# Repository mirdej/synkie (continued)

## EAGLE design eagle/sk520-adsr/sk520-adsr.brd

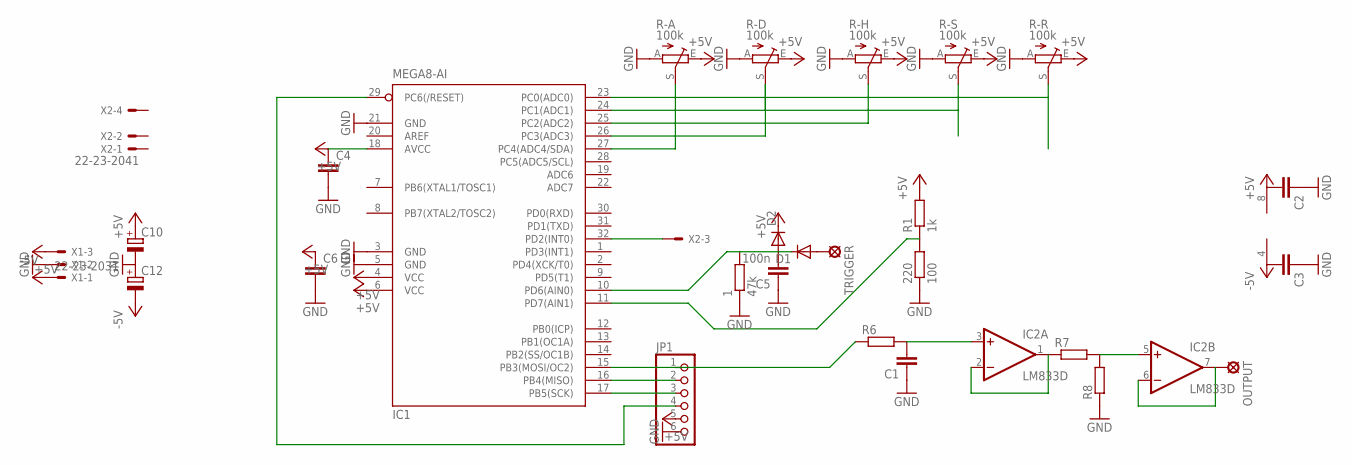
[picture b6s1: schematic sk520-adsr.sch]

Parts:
1: 47k; R1206
220: 100; R1206
C1, C2, C3, C4, C6: C-EUC1206; C1206
C5: 100n; C1206
C10, C12: CPOL-EUCT6032; CT6032
D1, D2: DIODE-MINIMELF; MINIMELF
IC1: MEGA8-AI; TQFP32-08
IC2: LM833D; SO08
JP1: PINHD-1X6; 1X06
OUTPUT: LSP11
R1: 1k; R1206
R6, R7, R8: R-EU_R1206; R1206
R-A: 100k; CIP20C-6MM
R-D: 100k; CIP20C-6MM
R-H: 100k; CIP20C-6MM
R-R: 100k; CIP20C-6MM
R-S: 100k; CIP20C-6MM
TRIGGER: LSP11
X1: 22-23-2031
X2: 22-23-2041

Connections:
+5V: C2.2, C4.1, C6.1, C10.+, D2.C, IC1.4 (VCC), IC1.6 (VCC), IC1.18 (AVCC), IC2.8 (V+), JP1.5, R1.2, R-A.E, R-D.E, R-H.E, R-R.E, R-S.E, X1.3
-5V: C3.2, C12.-, IC2.4 (V-), X1.1
GND: 1.1, 220.1, C1.1, C2.1, C3.1, C4.2, C5.1, C6.2, C10.-, C12.+, IC1.3 (GND), IC1.5 (GND), IC1.21 (GND), JP1.6, R8.1, R-A.A, R-D.A, R-H.A, R-R.A, R-S.A, X1.2
unnamed: IC1.15 (PB3(MOSI/OC2)), JP1.1, R6.1
unnamed: D1.A, TRIGGER.MP
unnamed: IC1.16 (PB4(MISO)), JP1.2
unnamed: IC1.17 (PB5(SCK)), JP1.3
unnamed: IC1.29 (PC6(/RESET)), JP1.4
unnamed: IC1.27 (PC4(ADC4/SDA)), R-A.S
unnamed: IC1.26 (PC3(ADC3)), R-D.S
unnamed: IC1.25 (PC2(ADC2)), R-H.S
unnamed: IC1.24 (PC1(ADC1)), R-S.S
unnamed: IC1.23 (PC0(ADC0)), R-R.S
unnamed: 1.2, C5.2, D1.C, D2.A, IC1.10 (PD6(AIN0))
unnamed: C1.2, IC2.3 (+IN), R6.2
unnamed: IC2.1 (OUT), IC2.2 (-IN), R7.1
unnamed: IC2.5 (+IN), R7.2, R8.2
unnamed: IC2.6 (-IN), IC2.7 (OUT), OUTPUT.MP
unnamed: 220.2, IC1.11 (PD7(AIN1)), R1.1
TRIGGER: IC1.32 (PD2(INT0)), X2.3

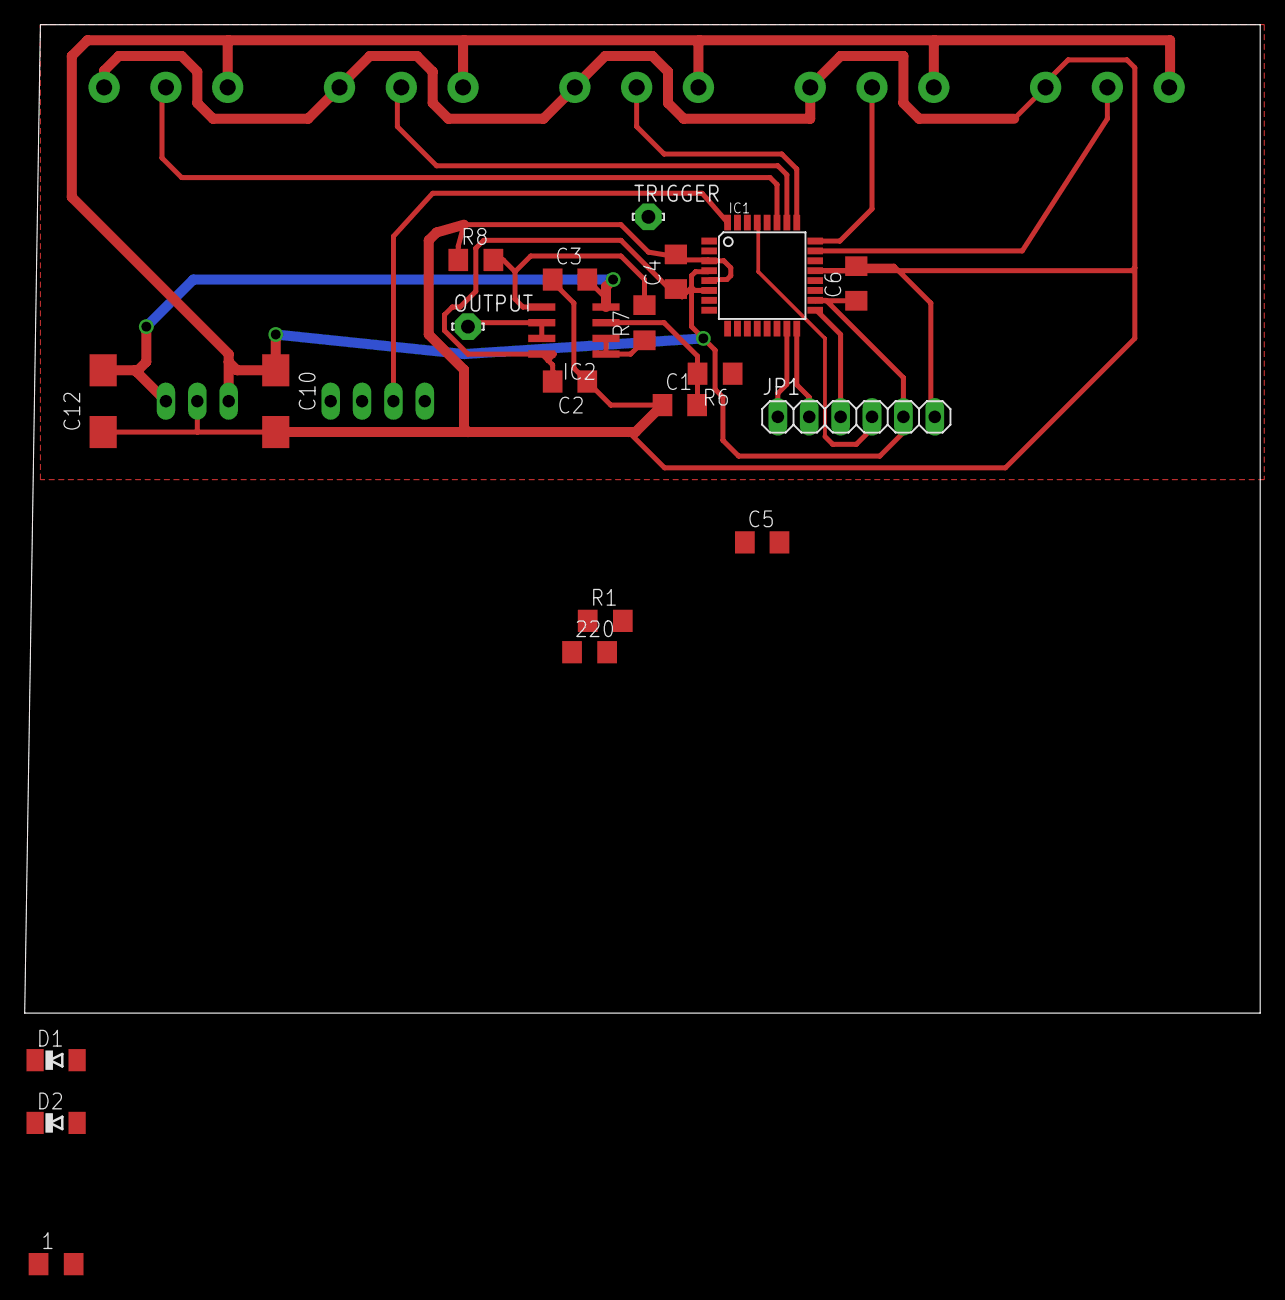
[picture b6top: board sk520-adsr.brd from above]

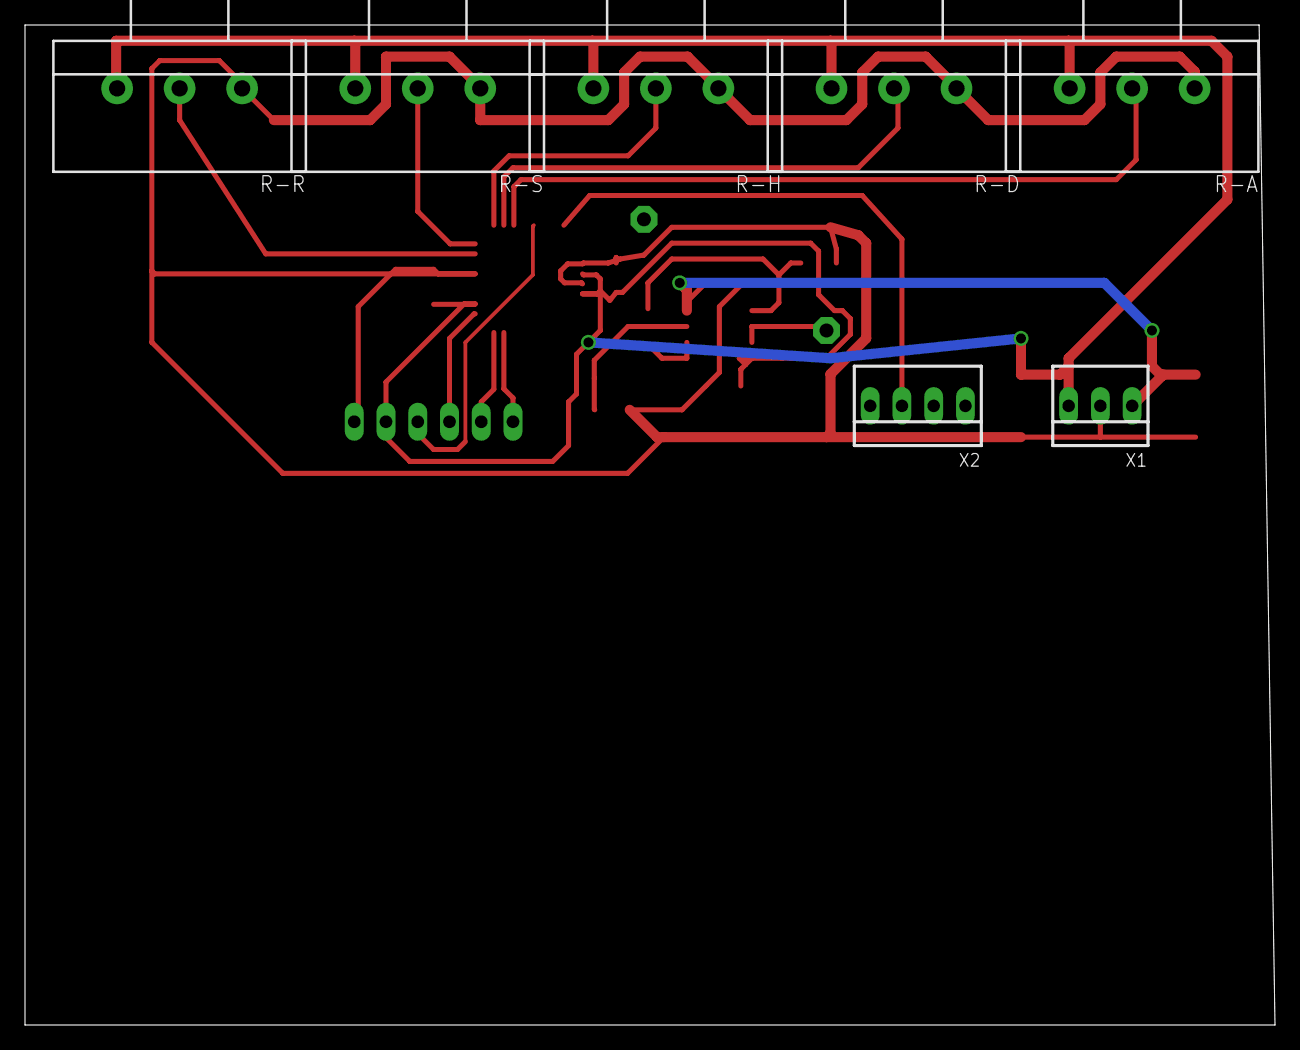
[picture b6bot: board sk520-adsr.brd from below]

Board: 2 copper layers, 100.0 x 80.0 mm, 28 parts (7 on the bottom side), 20 nets.

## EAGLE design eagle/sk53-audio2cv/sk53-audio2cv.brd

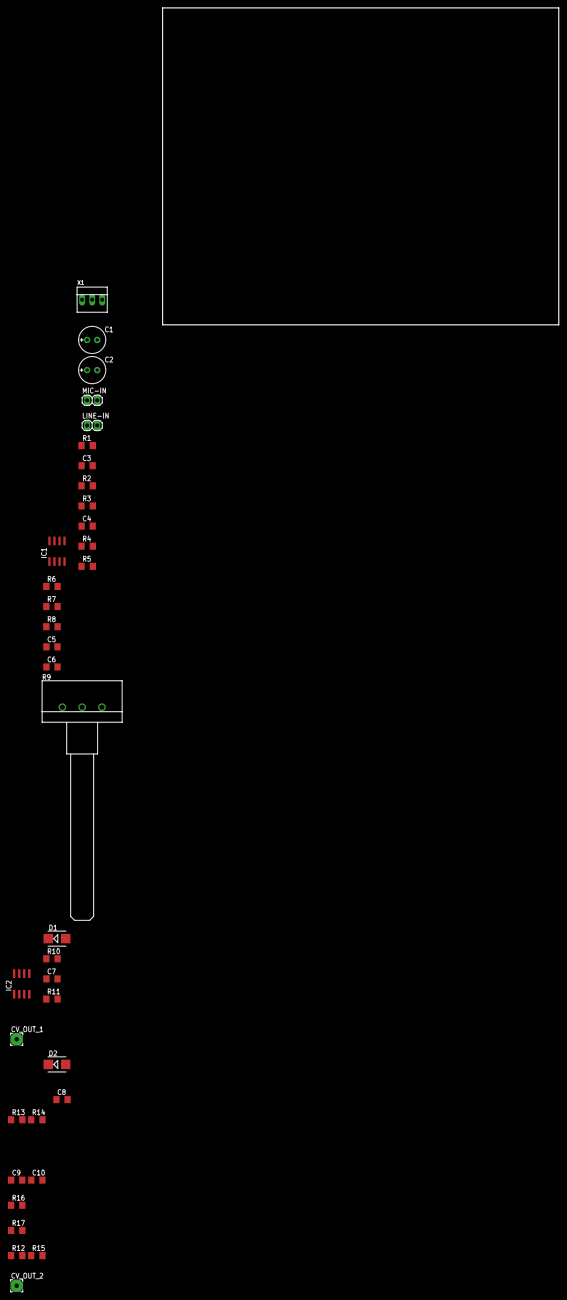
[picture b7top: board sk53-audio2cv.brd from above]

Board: 2 copper layers, 100.0 x 80.0 mm, 36 parts (0 on the bottom side), 20 nets, no tracks yet.

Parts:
C1, C2: 22u; E2,5-7
C3, C4: C1206
C5, C6, C7, C8, C9, C10: 100n; C1206
CV_OUT_1, CV_OUT_2: 3,17/1,1
D1, D2: SMB
IC1, IC2: LM833D; SO08
LINE-IN: 1X02
MIC-IN: 1X02
R1, R4: 47k; R1206
R2, R5, R7, R8: 1k; R1206
R3: 4k7; R1206
R6: 100k; R1206
R9: 100k; CIP20C-6MM
R10, R13: 10k; R1206
R11, R14: R1206
R12, R16: 300; R1206
R15, R17: 75; R1206
X1: 22-23-2031

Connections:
+5V: C1.+, C5.2, C9.2, IC1.8, IC2.8, R3.2, X1.1
-5V: C2.-, C6.2, C10.2, IC1.4, IC2.4, X1.3
GND: C1.-, C2.+, C5.1, C6.1, C7.2, C8.2, C9.1, C10.1, IC1.3, IC1.5, LINE-IN.2, MIC-IN.2, R1.1, R4.1, R11.2, R14.2, R15.1, R17.1, X1.2
unnamed: C3.2, LINE-IN.1, R1.2
unnamed: C3.1, R2.2
unnamed: C4.2, MIC-IN.1, R3.1
unnamed: C4.1, R4.2, R5.2
unnamed: IC1.2, R5.1, R6.2
unnamed: IC1.1, R6.1, R7.2
unnamed: IC1.6, R2.1, R7.1, R8.2
unnamed: R8.1, R9.A, R9.S
unnamed: D1.A, D2.A, IC1.7, R9.E
unnamed: D1.C, R10.2
unnamed: C7.1, IC2.5, R10.1, R11.1
unnamed: IC2.6, IC2.7, R16.1
unnamed: CV_OUT_2.1, R12.2, R15.2
unnamed: D2.C, R13.2
unnamed: C8.1, IC2.3, R13.1, R14.1
unnamed: IC2.1, IC2.2
unnamed: CV_OUT_1.1, R16.2, R17.2
